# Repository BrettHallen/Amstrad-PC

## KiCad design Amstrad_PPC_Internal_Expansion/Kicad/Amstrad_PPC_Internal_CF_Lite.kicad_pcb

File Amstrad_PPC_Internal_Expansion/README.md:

# Amstrad PPC XT CF Lite
Internal CF interface for the Amstrad PPC512/640.<br>

Replaces the internal modem board with a combination ISA interface & XT-IDE/Compact Flash interface.<br> 

Heavily based on [Sergey Kiselev's design](https://github.com/skiselev/xt-cf-lite-v4).<br>

Which is apparently a remake of [James Pearce's card](http://www.lo-tech.co.uk/wiki/XT-CF-lite).<br>

Changes requires for internal mounting in the Amstrad PPC:<br>
[1] The following signals are generated directly from the internal gate arrays and should be buffered with a non-inverting buffer (i.e. 72HC244): A00 to A07, ~MEMW, ~MEMR, ~IOW, ~IOR, RESET _(there are others but irrelevant for our purposes)_<br>
[2] The data signals (D0 to D7) are at CMOS levels and should be pulled up to TTL levels with 10KΩ resistors<br>
[3] The internal modem board we are replacing is roughly 200x120mm<br>
[4] Technically the PPC should be powered by the "expansion unit" and not the other way around ... don't tell anyone<br>

Currently untested ...<br><br>

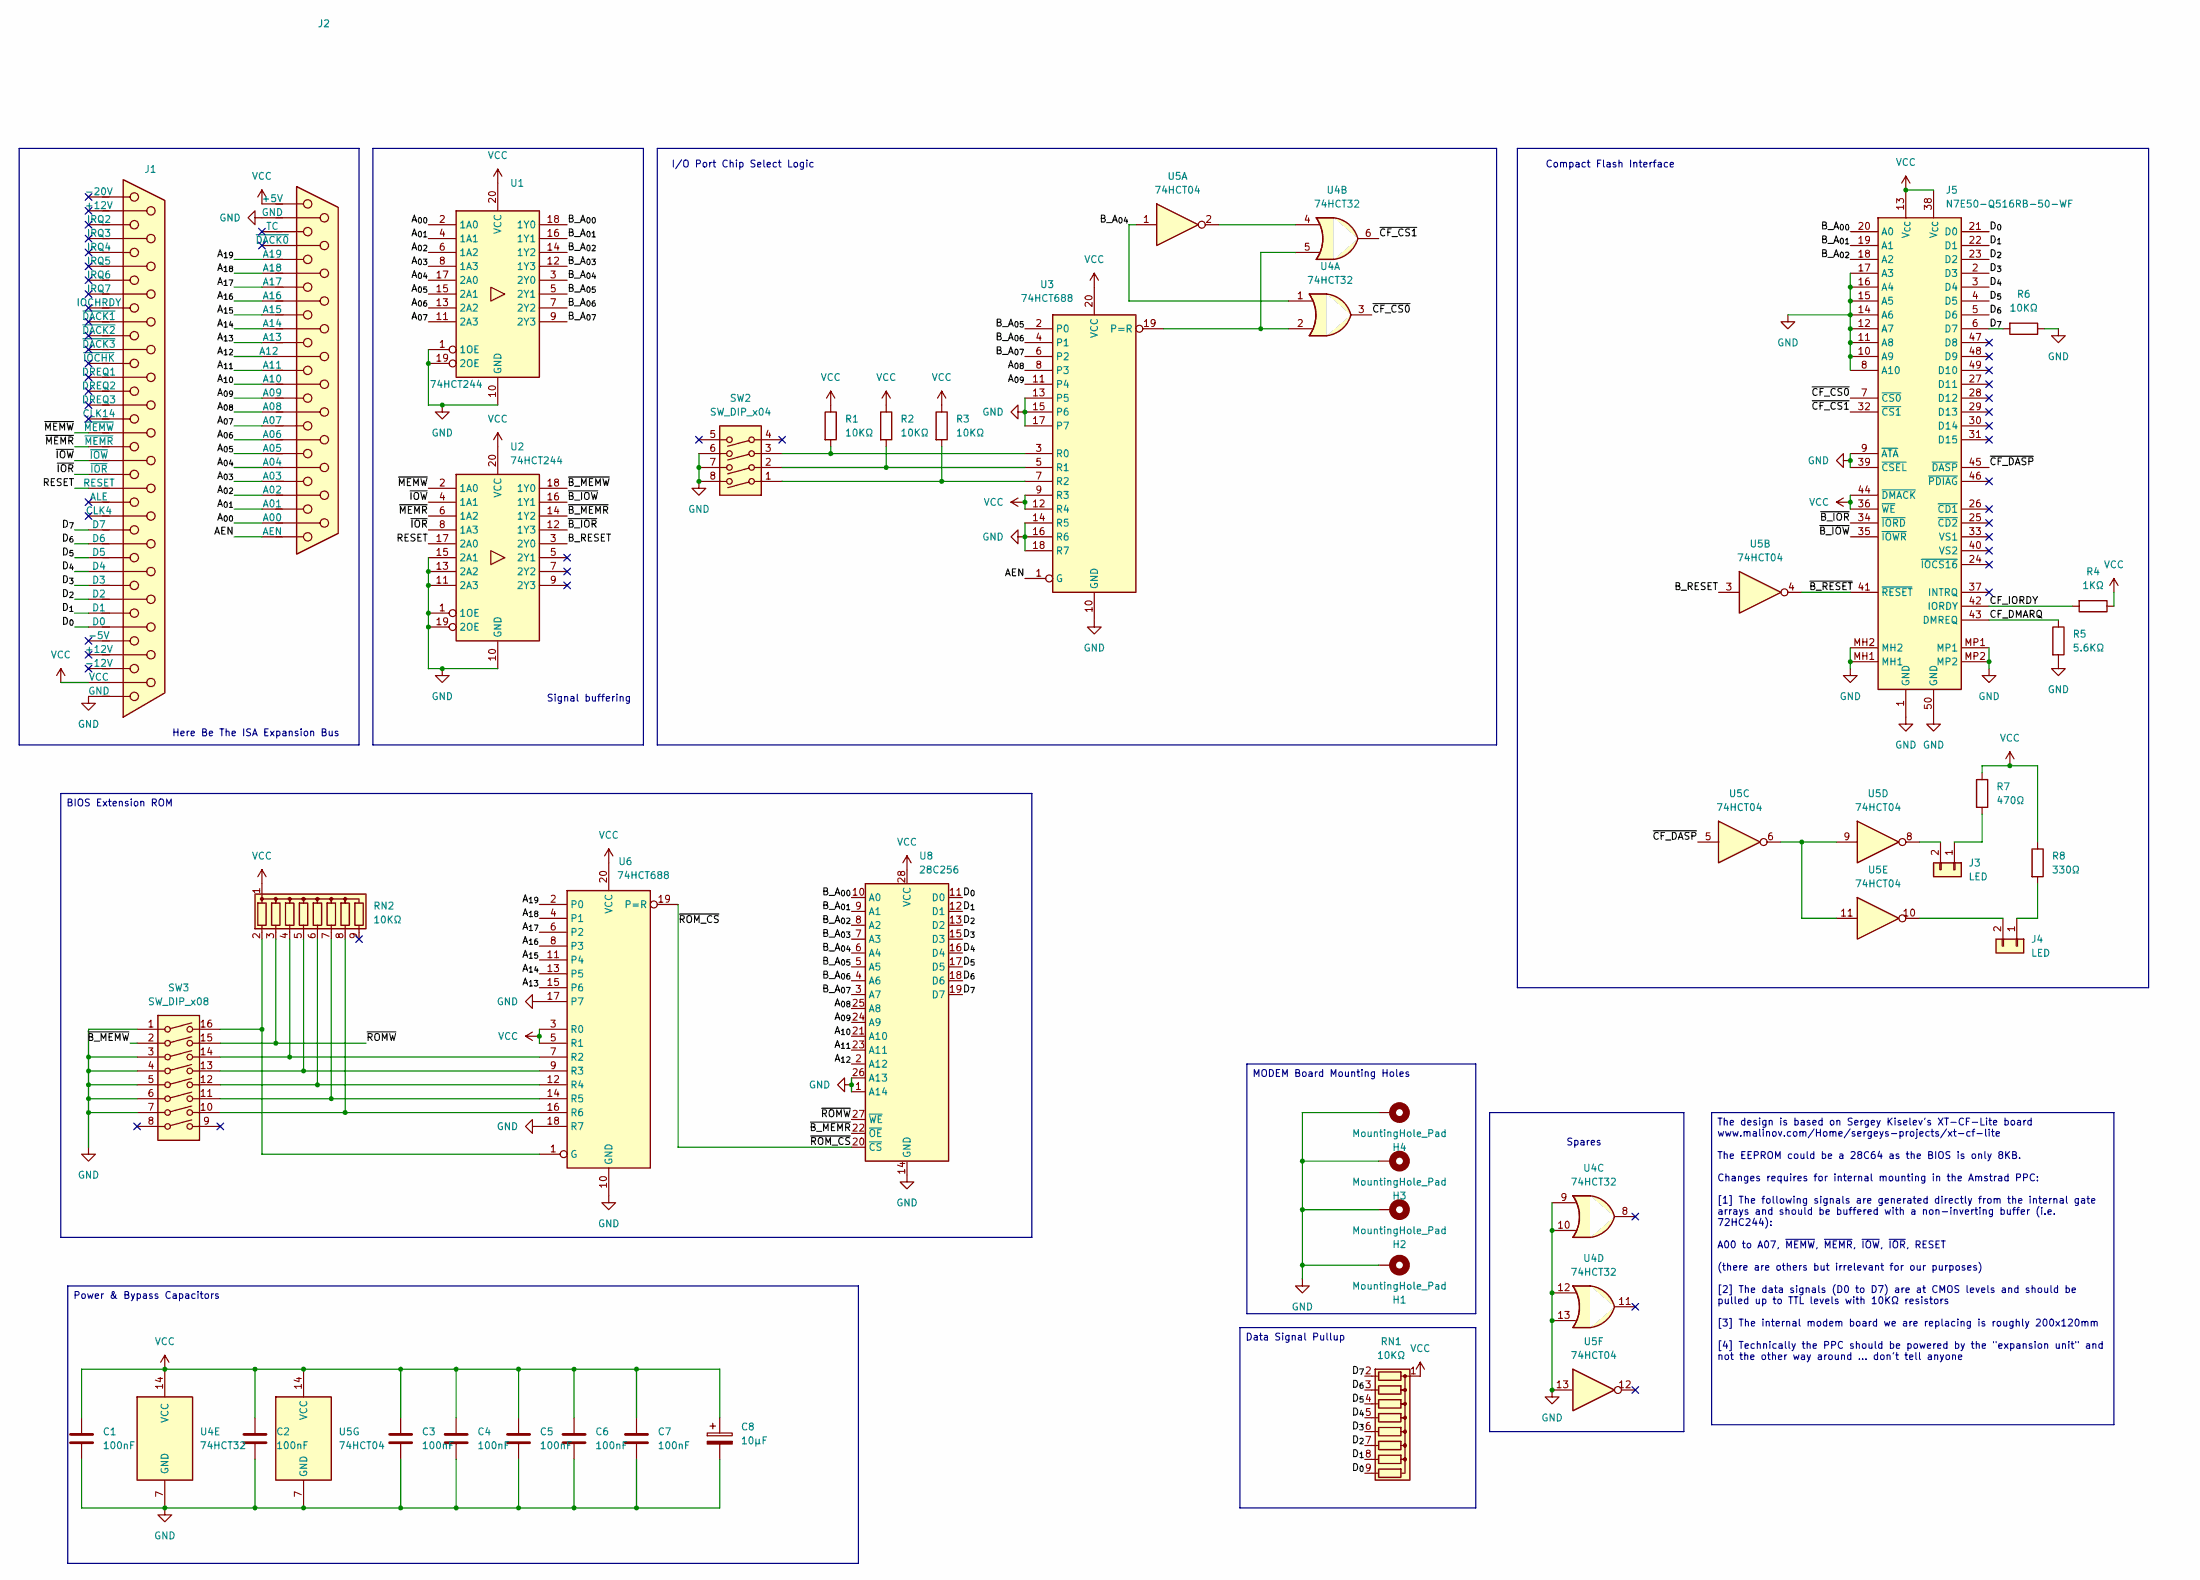
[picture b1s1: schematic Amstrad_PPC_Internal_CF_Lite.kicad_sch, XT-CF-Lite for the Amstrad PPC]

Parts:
C1, C2, C3, C4, C5, C6, C7: 100nF; C_Disc_D3.4mm_W2.1mm_P2.50mm
C8: 10µF; CP_Radial_D5.0mm_P2.50mm
H1, H2, H3, H4: MountingHole_Pad; MountingHole_6.4mm_M6_DIN965_Pad
J1: Amstrad_PPC_ISA_Connector_B; DSUB-37_Socket_EdgeMount_P2.77mm
J2: Amstrad_PPC_ISA_Connector_A; DSUB-25_Socket_EdgeMount_P2.77mm
J3, J4: LED; PinHeader_1x02_P2.54mm_Vertical
J5: N7E50-Q516RB-50-WF; N7E50Q516RB50WF; Mouser Part Number 517-N7E50-Q516B-50-W
R1, R2, R3, R6: 10KΩ; R_Axial_DIN0207_L6.3mm_D2.5mm_P7.62mm_Horizontal
R4: 1KΩ; R_Axial_DIN0207_L6.3mm_D2.5mm_P7.62mm_Horizontal
R5: 5.6KΩ; R_Axial_DIN0207_L6.3mm_D2.5mm_P7.62mm_Horizontal
R7: 470Ω; R_Axial_DIN0207_L6.3mm_D2.5mm_P7.62mm_Horizontal
R8: 330Ω; R_Axial_DIN0207_L6.3mm_D2.5mm_P7.62mm_Horizontal
RN1, RN2: 10KΩ; R_Array_SIP9
SW2: SW_DIP_x04; SW_DIP_SPSTx04_Slide_9.78x12.34mm_W7.62mm_P2.54mm
SW3: SW_DIP_x08; SW_DIP_SPSTx08_Slide_9.78x22.5mm_W7.62mm_P2.54mm
U1, U2: 74HCT244; DIP-20_W7.62mm
U3, U6: 74HCT688; DIP-20_W7.62mm
U4: 74HCT32; DIP-14_W7.62mm
U5: 74HCT04; DIP-14_W7.62mm
U8: 28C256; DIP-28_W15.24mm_Socket

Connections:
/AEN: J2.13 (AEN), U3.1 (G)
/A_{00}: J2.25 (A00), U1.2 (1A0)
/A_{01}: J2.12 (A01), U1.4 (1A1)
/A_{02}: J2.24 (A02), U1.6 (1A2)
/A_{03}: J2.11 (A03), U1.8 (1A3)
/A_{04}: J2.23 (A04), U1.17 (2A0)
/A_{05}: J2.10 (A05), U1.15 (2A1)
/A_{06}: J2.22 (A06), U1.13 (2A2)
/A_{07}: J2.9 (A07), U1.11 (2A3)
/A_{08}: J2.21 (A08), U3.8 (P3), U8.25 (A8)
/A_{09}: J2.8 (A09), U3.11 (P4), U8.24 (A9)
/A_{10}: J2.20 (A10), U8.21 (A10)
/A_{11}: J2.7 (A11), U8.23 (A11)
/A_{12}: J2.19 (A12), U8.2 (A12)
/A_{13}: J2.6 (A13), U6.15 (P6)
/A_{14}: J2.18 (A14), U6.13 (P5)
/A_{15}: J2.5 (A15), U6.11 (P4)
/A_{16}: J2.17 (A16), U6.8 (P3)
/A_{17}: J2.4 (A17), U6.6 (P2)
/A_{18}: J2.16 (A18), U6.4 (P1)
/A_{19}: J2.3 (A19), U6.2 (P0)
/B_A_{00}: J5.20 (A0), U1.18 (1Y0), U8.10 (A0)
/B_A_{01}: J5.19 (A1), U1.16 (1Y1), U8.9 (A1)
/B_A_{02}: J5.18 (A2), U1.14 (1Y2), U8.8 (A2)
/B_A_{03}: U1.12 (1Y3), U8.7 (A3)
/B_A_{04}: U1.3 (2Y0), U4.1, U5.1, U8.6 (A4)
/B_A_{05}: U1.5 (2Y1), U3.2 (P0), U8.5 (A5)
/B_A_{06}: U1.7 (2Y2), U3.4 (P1), U8.4 (A6)
/B_A_{07}: U1.9 (2Y3), U3.6 (P2), U8.3 (A7)
/B_RESET: U2.3 (2Y0), U5.3
/CF_DMARQ: J5.43 (DMREQ), R5.1
/CF_IORDY: J5.42 (IORDY), R4.2
/D_{0}: J1.35 (D0), J5.21 (D0), RN1.9 (R8), U8.11 (D0)
/D_{1}: J1.16 (D1), J5.22 (D1), RN1.8 (R7), U8.12 (D1)
/D_{2}: J1.34 (D2), J5.23 (D2), RN1.7 (R6), U8.13 (D2)
/D_{3}: J1.15 (D3), J5.2 (D3), RN1.6 (R5), U8.15 (D3)
/D_{4}: J1.33 (D4), J5.3 (D4), RN1.5 (R4), U8.16 (D4)
/D_{5}: J1.14 (D5), J5.4 (D5), RN1.4 (R3), U8.17 (D5)
/D_{6}: J1.32 (D6), J5.5 (D6), RN1.3 (R2), U8.18 (D6)
/D_{7}: J1.13 (D7), J5.6 (D7), R6.2, RN1.2 (R1), U8.19 (D7)
/RESET: J1.30 (RESET), U2.17 (2A0)
/~B_IOR: J5.34 (~IORD), U2.12 (1Y3)
/~B_IOW: J5.35 (~IOWR), U2.16 (1Y1)
/~B_MEMR: U2.14 (1Y2), U8.22 (~OE)
/~B_MEMW: SW3.2, U2.18 (1Y0)
/~B_RESET: J5.41 (~RESET), U5.4
/~CF_CS0: J5.7 (~CS0), U4.3
/~CF_CS1: J5.32 (~CS1), U4.6
/~CF_DASP: J5.45 (~DASP), U5.5
/~IOR: J1.11 (~IOR), U2.8 (1A3)
/~IOW: J1.29 (~IOW), U2.4 (1A1)
/~MEMR: J1.10 (~MEMR), U2.6 (1A2)
/~MEMW: J1.28 (~MEMW), U2.2 (1A0)
/~ROMW: RN2.3 (R2), SW3.15, U8.27 (~WE)
/~ROM_CS: U6.19 (P=R), U8.20 (~CS)
GND: C1.2, C2.2, C3.2, C4.2, C5.2, C6.2, C7.2, C8.2, H1.1, H2.1, H3.1, H4.1, J1.19 (GND), J2.14 (GND), J5.1 (GND), J5.8 (A10), J5.9 (~ATA), J5.10 (A9), J5.11 (A8), J5.12 (A7), J5.14 (A6), J5.15 (A5), J5.16 (A4), J5.17 (A3), J5.39 (~CSEL), J5.50 (GND), J5.MH1, J5.MH2, J5.MP1, J5.MP2, R5.2, R6.1, SW2.6, SW2.7, SW2.8, SW3.1, SW3.3, SW3.4, SW3.5, SW3.6, SW3.7, U1.1 (1OE), U1.10 (GND), U1.19 (2OE), U2.1 (1OE), U2.10 (GND), U2.11 (2A3), U2.13 (2A2), U2.15 (2A1), U2.19 (2OE), U3.10 (GND), U3.13 (P5), U3.14 (R5), U3.15 (P6), U3.16 (R6), U3.17 (P7), U3.18 (R7), U4.7 (GND), U4.9, U4.10, U4.12, U4.13, U5.7 (GND), U5.13, U6.10 (GND), U6.17 (P7), U6.18 (R7), U8.1 (A14), U8.14 (GND), U8.26 (A13); also elsewhere on the board
unnamed: J3.1, R7.2
unnamed: J3.2, U5.8
unnamed: J4.1, R8.2
unnamed: J4.2, U5.10
unnamed: RN2.2 (R1), SW3.16, U6.1 (G)
unnamed: RN2.4 (R3), SW3.14, U6.7 (R2)
unnamed: RN2.5 (R4), SW3.13, U6.9 (R3)
unnamed: RN2.6 (R5), SW3.12, U6.12 (R4)
unnamed: RN2.7 (R6), SW3.11, U6.14 (R5)
unnamed: RN2.8 (R7), SW3.10, U6.16 (R6)
unnamed: U3.19 (P=R), U4.2, U4.5
unnamed: R1.2, SW2.3, U3.3 (R0)
unnamed: R2.2, SW2.2, U3.5 (R1)
unnamed: R3.2, SW2.1, U3.7 (R2)
unnamed: U4.4, U5.2
unnamed: U5.6, U5.9, U5.11
VCC: C1.1, C2.1, C3.1, C4.1, C5.1, C6.1, C7.1, C8.1, J1.37 (VCC), J2.1 (+5V), J5.13 (V_{CC}), J5.36 (~WE), J5.38 (V_{CC}), J5.44 (~DMACK), R1.1, R2.1, R3.1, R4.1, R7.1, R8.1, RN1.1 (common), RN2.1 (common), U1.20 (VCC), U2.20 (VCC), U3.9 (R3), U3.12 (R4), U3.20 (VCC), U4.14 (VCC), U5.14 (VCC), U6.3 (R0), U6.5 (R1), U6.20 (VCC), U8.28 (VCC)

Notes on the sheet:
Signal buffering
Spares
Compact Flash Interface
I/O Port Chip Select Logic
Here Be The ISA Expansion Bus
Data Signal Pullup
The design is based on Sergey Kiselev's XT-CF-Lite board www.malinov.com/Home/sergeys-projects/xt-cf-lite The EEPROM could be a 28C64 as the BIOS is only 8KB. Changes requires for internal mounting in the Amstrad PPC: [1] The following signals are generated directly from the internal gate arrays an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
Power & Bypass Capacitors
BIOS Extension ROM
MODEM Board Mounting Holes

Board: 2 copper layers, 39 parts (0 on the bottom side), 73 nets, no tracks yet.

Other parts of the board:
H5, H6, H7: MountingHole_Pad; MountingHole_3.2mm_M3_DIN965_Pad

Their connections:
GND: H5.1, H6.1, H7.1; also elsewhere on the board

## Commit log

2026-05-28 Starting again ... initial schematic cleanup
    Schematic is now cleaned up, no errors
    Next will be PCB layout
